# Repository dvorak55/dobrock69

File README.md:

# dobrock69
 Dvorak Oriented Bunkatsu Rock’n’roll Keyboard!

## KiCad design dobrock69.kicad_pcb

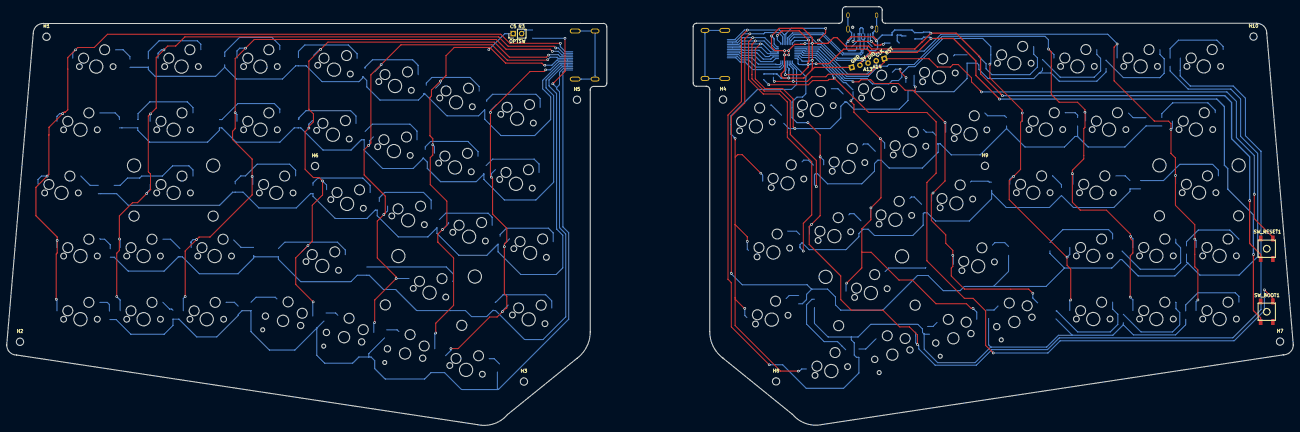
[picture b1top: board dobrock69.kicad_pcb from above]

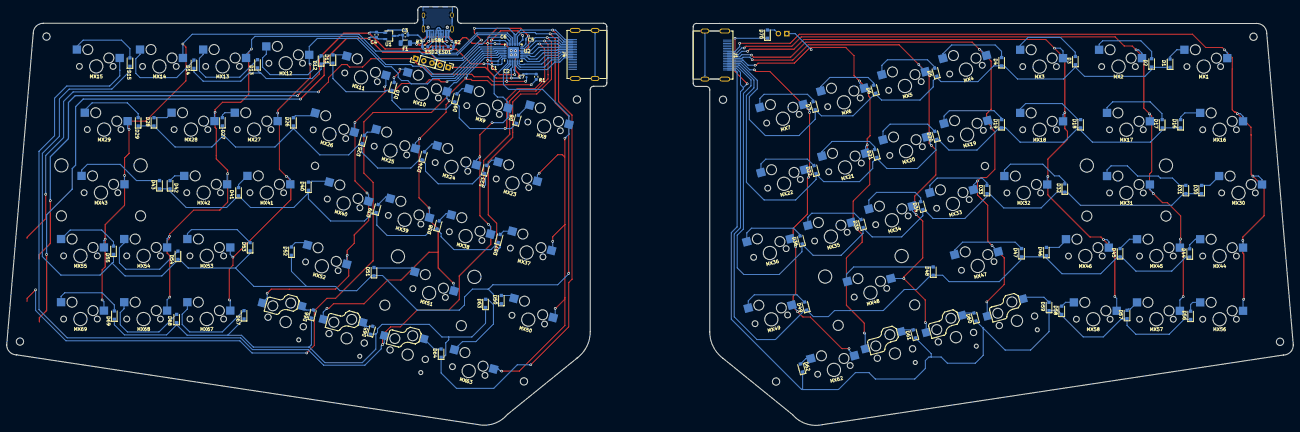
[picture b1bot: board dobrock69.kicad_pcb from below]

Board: 2 copper layers, 388.0 x 126.3 mm, 172 parts (90 on the bottom side), 101 nets.

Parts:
C1, C2, C5, C6, C7: 100nF; C_0402_1005Metric
C3, C4: 1uF; C_0603_1608Metric
D1, D2, D3, D4, D5, D6, D7, D8, D9, D10, D11, D12, D13, D14, D15, D16, D17, D18, D19, D20, D21, D22, D23, D24, D25, D26, D27, D28, D29, D30, D31, D32, D33, D34, D35, D36, D37, D38, D39, D40, D41, D42, D43, D44, D45, D46, D47, D48, D49, D50, D51, D52, D53, D54, D55, D56, D57, D58, D59, D60, D61, D62, D63, D64, D65, D66, D67, D68, D69, D70: SOD-123; D_SOD-323_HandSoldering
ESD1, ESD2: ESDAXLC6-1BT2; D_0402_1005Metric
F1: nSMD025; Fuse_1206_3216Metric
H1, H2, H3, H4, H5, H6, H7, H8, H9, H10: MountingHole; MountingHole_2.2mm_M2
J1, J4: HDMI_A_1.4; HDMI_A_Sofng_019S
J2, J5: Conn_01x02; PinHeader_1x02_P2.54mm_Vertical
J3: Conn_01x03; PinHeader_1x03_P2.54mm_Vertical
MX1, MX3, MX4, MX5, MX6, MX7, MX8, MX9, MX10, MX11, MX12, MX13, MX14, MX15, MX16, MX18, MX19, MX20, MX21, MX22, MX23, MX24, MX25, MX26, MX27, MX28, MX30, MX32, MX33, MX34, MX35, MX36, MX37, MX38, MX39, MX40, MX41, MX42, MX44, MX45, MX49, MX50, MX53, MX54, MX55, MX56, MX57, MX58, MX62, MX63, MX67, MX68, MX69: MX-NoLED; MXOnly-1U-Hotswap
MX2: MX-NoLED; MXOnly-1.5U-Hotswap
MX17, MX29: MX-NoLED; MXOnly-1.75U-Hotswap
MX31, MX43, MX48, MX51: MX-NoLED; MXOnly-2.25U-Hotswap-ReversedStabilizers
MX46, MX47, MX52: MX-NoLED; MXOnly-1.25U-Hotswap
MX59, MX60, MX61, MX64, MX65, MX66: MX-NoLED; KailhChoc-1U-hotswap
R1: 10k; R_0603_1608Metric
R2, R3: 5.1k; R_0603_1608Metric
SW_BOOT1: TS-1187A-B-A-B; SKQGADE010
SW_RESET1: TS-1187A-B-A-B; SKQGADE010
U1: XC6206P332MR; TSOT-23
U2: STM32L072KBUx; QFN-32-1EP_5x5mm_P0.5mm_EP3.45x3.45mm
USB1: HRO-TYPE-C-31-M-12; HRO-TYPE-C-31-M-12-HandSoldering

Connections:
+3V3: C1.1, C2.1, C4.1, C5.1, C6.1, J2.2, SW_BOOT1.1, U1.2, U2.5, U2.17, U2.24, U2.32
COL0: J1.12, J4.12, MX1.1, MX16.1, MX30.1, MX44.1, MX56.1, U2.6
COL1: J1.11, J4.11, MX2.1, MX17.1, MX31.1, MX45.1, MX57.1, U2.7
COL2: J1.10, J4.10, MX3.1, MX18.1, MX32.1, MX46.1, MX58.1, U2.8
COL3: J1.9, J4.9, MX4.1, MX19.1, MX33.1, MX47.1, MX59.1, U2.9
COL4: J1.8, J4.8, MX5.1, MX20.1, MX34.1, MX48.1, MX60.1, U2.10
COL5: J1.7, J4.7, J5.1, MX6.1, MX21.1, MX35.1, MX61.1, U2.11
COL6: J1.6, J4.6, MX7.1, MX22.1, MX36.1, MX49.1, MX62.1, U2.12
COL7: MX8.1, MX23.1, MX37.1, MX50.1, MX63.1, U2.2
COL8: MX9.1, MX15.1, MX24.1, MX38.1, MX64.1, U2.1
COL9: MX10.1, MX25.1, MX39.1, MX51.1, MX65.1, U2.29
COL10: MX11.1, MX26.1, MX40.1, MX52.1, MX66.1, U2.28
COL11: MX12.1, MX27.1, MX41.1, MX53.1, MX67.1, U2.27
COL12: MX13.1, MX28.1, MX42.1, MX54.1, MX68.1, U2.26
COL13: MX14.1, MX29.1, MX43.1, MX55.1, MX69.1, U2.20
D+: ESD2.2, U2.22, USB1.6, USB1.8
D-: ESD1.1, U2.21, USB1.5, USB1.7
GND: C1.2, C2.2, C3.2, C4.2, C5.2, C6.2, C7.1, ESD1.2, ESD2.1, J2.1, R1.2, R2.2, R3.2, SW_RESET1.1, U1.1, U2.4, U2.16, U2.31, U2.33, USB1.1, USB1.12, USB1.13
NRST: C7.2, J3.1, SW_RESET1.2, U2.3
unnamed: C3.1, F1.1, U1.3
unnamed: D1.2, MX1.2
unnamed: D2.2, MX2.2
unnamed: D3.2, MX3.2
unnamed: D4.2, MX4.2
unnamed: D5.2, MX5.2
unnamed: D6.2, MX6.2
unnamed: D7.2, MX7.2
unnamed: D8.2, MX8.2
unnamed: D9.2, MX9.2
unnamed: D10.2, MX10.2
unnamed: D11.2, MX11.2
unnamed: D12.2, MX12.2
unnamed: D13.2, MX13.2
unnamed: D14.2, MX14.2
unnamed: D15.2, MX15.2
unnamed: D16.2, MX16.2
unnamed: D17.2, MX17.2
unnamed: D18.2, MX18.2
unnamed: D19.2, MX19.2
unnamed: D20.2, MX20.2
unnamed: D21.2, MX21.2
unnamed: D22.2, MX22.2
unnamed: D23.2, MX23.2
unnamed: D24.2, MX24.2
unnamed: D25.2, MX25.2
unnamed: D26.2, MX26.2
unnamed: D27.2, MX27.2
unnamed: D28.2, MX28.2
unnamed: D29.2, MX29.2
unnamed: D30.2, MX30.2
unnamed: D31.2, MX31.2
unnamed: D32.2, MX32.2
unnamed: D33.2, MX33.2
unnamed: D34.2, MX34.2
unnamed: D35.2, MX35.2
unnamed: D36.2, MX36.2
unnamed: D37.2, MX37.2
unnamed: D38.2, MX38.2
unnamed: D39.2, MX39.2
unnamed: D40.2, MX40.2
unnamed: D41.2, MX41.2
unnamed: D42.2, MX42.2
unnamed: D43.2, MX43.2
unnamed: D44.2, MX44.2
unnamed: D45.2, MX45.2
unnamed: D46.2, MX46.2
unnamed: D47.2, MX47.2
unnamed: D48.2, MX48.2
unnamed: D49.2, MX49.2
unnamed: D50.2, MX50.2
unnamed: D51.2, MX51.2
unnamed: D52.2, MX52.2
unnamed: D53.2, MX53.2
unnamed: D54.2, MX54.2
unnamed: D55.2, MX55.2
unnamed: D56.2, MX56.2
unnamed: D57.2, MX57.2
unnamed: D58.2, MX58.2
unnamed: D59.2, MX59.2
unnamed: D60.2, MX60.2
unnamed: D61.2, MX61.2
unnamed: D62.2, MX62.2
unnamed: D63.2, MX63.2
unnamed: D64.2, MX64.2
unnamed: D65.2, MX65.2
unnamed: D66.2, MX66.2
unnamed: D67.2, MX67.2
unnamed: D68.2, MX68.2
unnamed: D69.2, MX69.2
unnamed: D70.2, J5.2
unnamed: F1.2, USB1.2, USB1.11
unnamed: R1.1, SW_BOOT1.2, U2.30
unnamed: R2.1, USB1.4
unnamed: R3.1, USB1.10
ROW0: D1.1, D2.1, D3.1, D4.1, D5.1, D6.1, D7.1, D8.1, D9.1, D10.1, D11.1, D12.1, D13.1, D14.1, J1.5, J4.5, U2.13
ROW1: D16.1, D17.1, D18.1, D19.1, D20.1, D21.1, D22.1, D23.1, D24.1, D25.1, D26.1, D27.1, D28.1, D29.1, J1.4, J4.4, U2.14
ROW2: D30.1, D31.1, D32.1, D33.1, D34.1, D35.1, D36.1, D37.1, D38.1, D39.1, D40.1, D41.1, D42.1, D43.1, J1.3, J4.3, U2.15
ROW3: D15.1, D44.1, D45.1, D46.1, D47.1, D48.1, D49.1, D50.1, D51.1, D52.1, D53.1, D54.1, D55.1, D70.1, J1.2, J4.2, U2.18
ROW4: D56.1, D57.1, D58.1, D59.1, D60.1, D61.1, D62.1, D63.1, D64.1, D65.1, D66.1, D67.1, D68.1, D69.1, J1.1, J4.1, U2.19
SWCLK: J3.2, U2.25
SWDIO: J3.3, U2.23

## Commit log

2020-09-14 add keylayout draft
2020-09-14 initialize project
2020-09-27 add submodules
2020-09-27 add footprint libraries
2020-09-27 almost done pcb schematic
2020-09-28 PCB switch daitai haichi shita
2020-09-30 pcb susunda
2020-10-03 pcb haisen susunda
2020-10-12 atosukosi
2020-11-06 Dobrock69 kansei!
2020-11-06 add qmk source
2020-12-22 Footprint add
    Dobrock69に使っているHDMI端子のフットプリントが足りなかったので追加しました。
